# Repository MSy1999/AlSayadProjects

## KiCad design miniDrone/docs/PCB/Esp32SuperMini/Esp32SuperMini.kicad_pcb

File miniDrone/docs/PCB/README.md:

# MiniDrone PCB schematic

Open `Esp32SuperMini/Esp32SuperMini.kicad_pro` in KiCad 10, then open its
schematic. If the schematic is already open, close and reopen it so KiCad
loads the updated file. The original empty schematic is saved in
`Esp32SuperMini/references/original-empty.kicad_sch`.

This is a carrier for the existing ESP32-C3 Super Mini and GY-521/MPU6050 boards,
using four BC337 low-side motor switches and your 1S 3.7 V, 400 mAh battery.
The schematic and routed PCB are prototypes for review; module fit and motor
current ratings still require validation before manufacture.

Revision D uses a 70 x 70 mm board with extra space for hand soldering and
through-hole carrier components: ordinary 1/4 W axial resistors,
leaded capacitors and diodes, BC337s, and solderable header/socket holes for both
modules. No SMD assembly is required on the carrier. See
[hand assembly and part sizes](HAND_ASSEMBLY.md). The previous SMD revision is
archived under `Esp32SuperMini/references/revision-B-SMD/`.

The schematic uses one A2 sheet with continuous visible wires between the battery,
power components, controller, IMU and all four motor stages. Labels name the
wires; no connection relies on matching labels. A dot marks a joined branch;
crossing wires without a dot remain separate. The controller symbol now groups
its pins by function to simplify wiring, while preserving the physical header
pad numbers listed below.

## Files

- `Esp32SuperMini.kicad_sch`: editable schematic with all four motor stages.
- `MiniDrone.kicad_sym`: project-local Super Mini and GY-521 module symbols.
- `MiniDrone.pretty/ESP32_C3_SuperMini_THT.kicad_mod`: provisional carrier footprint.
- `sym-lib-table` and `fp-lib-table`: relative library paths; no global installation needed.
- `preview/Esp32SuperMini.svg` and `.png`: rendered schematic previews.
- `BOM.csv`: components, assigned footprints and unresolved design notes.
- `MiniDrone.net.xml`: exported electrical connectivity.
- `erc-report.json`: KiCad electrical rules report.

Paths above are relative to `Esp32SuperMini/`. The project now includes a routed
70 x 70 mm PCB with two copper layers, ground pours, an antenna copper keepout,
four M2 mounting holes and labeled motor connectors at the corners. See
[PCB layout details](PCB_LAYOUT.md) for geometry, previews and validation results.

## If KiCad reports the Super Mini footprint is not found

The project library is `MiniDrone`, with path `${KIPRJMOD}/MiniDrone.pretty`.
If the editors were already open when the library files were created, refresh
the loaded table:

1. Close the **Update PCB from Schematic** dialog.
2. In PCB Editor, open **Preferences > Manage Footprint Libraries** and select
   **Project Specific Libraries**. Confirm that `MiniDrone` is enabled and its
   path is `${KIPRJMOD}/MiniDrone.pretty`.
3. Click **OK** to reload the footprint libraries, then press **F8** again.

This refresh was verified in the running KiCad session: U1 was found and the
update preview reported zero warnings and zero errors. Keep the `.pretty`
directory and `fp-lib-table` alongside the project when copying it elsewhere.

## The Super Mini symbol

The Super Mini is a development board, not the ESP32-C3 IC and not an
ESP32-C3-MINI-1 RF module. Those components have different pinouts and footprints.
Use `MiniDrone:ESP32_C3_SUPER_MINI` in this project. It represents the headers;
the regulator, USB connector, crystal, reset, boot button and antenna remain on
the existing plug-in board.

Looking from the top with the USB connector at the top:

| Left pad, top to bottom | Signal | Right pad, top to bottom | Signal |
| --- | --- | --- | --- |
| 1 | GPIO5 / IMU SCL | 16 | 5V |
| 2 | GPIO6 / M1 front left | 15 | GND |
| 3 | GPIO7 / M2 front right | 14 | 3V3 |
| 4 | GPIO8 / unused | 13 | GPIO4 / IMU SDA |
| 5 | GPIO9 / unused | 12 | GPIO3 / unused |
| 6 | GPIO10 / M3 rear right | 11 | GPIO2 / unused |
| 7 | GPIO20 / M4 rear left | 10 | GPIO1 / unused |
| 8 | GPIO21 / unused | 9 | GPIO0 / battery ADC |

These are carrier pad numbers, not chip pin numbers. They match the project
pinout image and firmware. Before making a board, measure the physical Super
Mini: this draft assumes 2.54 mm header pitch, 15.24 mm row spacing and an
18 x 22.5 mm board outline. Clone dimensions can differ. Check the USB overhang
and socket height. The antenna area is marked on `Dwgs.User`; create an actual
all-layer copper/track/via keepout during layout and verify its extent against
the physical antenna. The library drawing alone is not an enforced keepout;
the routed PCB includes a separate all-copper-layer rule area at the antenna.

U2 uses the assumed GY-521 header order VCC, GND, SCL, SDA, XDA, XCL, AD0, INT.
Verify this order on your board. Its footprint describes the 8-pin header only;
the module outline and mounting holes have not been measured.

## Power circuit

Battery positive -> J1 pin 1 -> external main switch SW1 -> `VBAT_SW`.
The four motor positive terminals connect to `VBAT_SW`; motor negative terminals
connect to their BC337 collectors. All emitters and logic grounds share GND.

J2 is a **wired interface to an external regulated 5 V boost module**, not the
footprint of a particular regulator. Pin 1 = battery input positive, 2 = input
ground, 3 = regulated 5 V output, 4 = output ground. Choose a module verified to
deliver at least 0.5 A at 5 V across the usable 1S battery range. Confirm its pin
order and connect with wires as needed. Its internal circuit is not implemented
on this carrier.

JP1 connects the boost output to the Super Mini's 5V input; its existing onboard
regulator supplies 3V3 to the controller and sensor. This deliberately uses the
development board's 5V input rather than assuming its regulator tolerates power
injected into 3V3. It differs from the earlier generic buck-boost proposal in
`../WIRING.md`.

- Battery operation: USB unplugged, JP1 removable shunt installed.
- USB programming: battery switch OFF, JP1 shunt REMOVED, then connect USB.
- JP1 is a manual isolation link, not automatic USB/battery power OR-ing.

The battery must have appropriate protection and discharge capability. Capacity
alone does not specify discharge current. No charger, automatic low-voltage
cutoff or reverse-polarity protection is included. The current sensor-monitor
firmware does not sample the battery divider or implement battery protection.

## BC337 motor drivers: values to verify

Each channel has a 330 ohm series base resistor (provisional), 10 kohm
base-emitter pulldown, leaded 1N5819 Schottky flyback diode (provisional), and 100 nF
ceramic suppression capacitor. The diode cathode/striped end goes to battery
positive and its anode goes to the collector/motor negative. Place the 100 nF
at the physical motor terminals; a distant PCB capacitor is not equivalent.

The selected BC337 footprint assumes onsemi's pin numbering: 1 collector,
2 base, 3 emitter. Verify the datasheet for your actual supplier. Do not reuse
a MOSFET pin assignment for a BC337.

At 3.3 V, 330 ohm gives roughly 6-8 mA of base drive depending on the base
voltage. This does not guarantee saturation at the unknown motor startup or
stall current. The onsemi BC337 datasheet specifies its saturation test at
500 mA collector current with 50 mA base current; the 800 mA absolute maximum
collector rating is not a practical design target. Do not reduce the resistor
to demand that base current directly from an ESP32 pin. Measure startup/stall
current, transistor voltage drop and temperature; use a suitable 3.3 V
logic-level MOSFET or proper driver if the BC337 stage is insufficient.

The 1N5819 selection, main switch, battery/motor connectors, copper widths and
battery discharge rating must also be checked against measured current. The
2.54 mm header footprints are placeholders for prototype wiring; they are not
verified high-current connector selections. C1's 470 uF value is a starting
point for measuring motor-induced supply transients, not a validated result.

R9/R10 are marked DNP in KiCad. Populate the optional 4.7 kohm I2C pull-ups only
if the GY-521 does not already supply suitable pull-ups to 3.3 V.

## Validation and regeneration

Validated with KiCad CLI 10.0.7: schematic loaded, SVG exported, and ERC produced
zero errors and zero warnings. `validate_schematic.py` checks the exported nets
against `main/board.h`, all four driver topologies, diode polarity, controller
power, sensor connections and battery divider. It also checks that every
assigned footprint exists. These checks do not validate thermal ratings or fit.
Revision B also compares every exported net's component/pin membership against
revision A and checks that there are no repeated or off-sheet labels, so the
connections are preserved using the visible wires.

`generate_schematic.py` regenerates the schematic, custom library, footprint
and BOM. **It overwrites the generated schematic**, so save manual edits
elsewhere before running it. `inspect_symbols.py` supplies its library reader.
`wired_layout.py` defines the fully connected page arrangement. The generator
uses KiCad's standard symbol libraries at the installed Windows
KiCad 10 path; edit `BASE` if using another installation.

```powershell
python docs/PCB/generate_schematic.py
& 'C:\Program Files\KiCad\10.0\bin\kicad-cli.exe' sch erc --format json --output docs/PCB/Esp32SuperMini/erc-report.json docs/PCB/Esp32SuperMini/Esp32SuperMini.kicad_sch
& 'C:\Program Files\KiCad\10.0\bin\kicad-cli.exe' sch export netlist --format kicadxml --output docs/PCB/Esp32SuperMini/MiniDrone.net.xml docs/PCB/Esp32SuperMini/Esp32SuperMini.kicad_sch
& 'C:\Program Files\KiCad\10.0\bin\kicad-cli.exe' sch export svg --output docs/PCB/Esp32SuperMini/preview docs/PCB/Esp32SuperMini/Esp32SuperMini.kicad_sch
python docs/PCB/validate_schematic.py
python docs/PCB/render_preview.py
```

The optional PNG renderer needs `resvg-py`; the editable schematic and SVG do
not depend on it. The generator makes no firmware changes.

## Circuit references

- [Super Mini pinout and board notes in Apache NuttX](https://nuttx.incubator.apache.org/docs/latest/platforms/risc-v/esp32c3/boards/esp32c3-supermini/index.html).
- [Supplier-hosted Super Mini pinout/schematic PDF](https://dl.artronshop.co.th/ESP32-C3%20SuperMini%20datasheet.pdf): a reference link for comparing your board variant; the remote PDF download timed out in this session, so it was not used to verify internal circuitry.
- [ded811's editable KiCad Super Mini circuit](https://github.com/ded811/ESP32-C3-Super-Mini-Kicad): a third-party redesign with antenna changes, not guaranteed identical to the purchased board.
- [Espressif ESP32-C3 hardware design checklist](https://docs.espressif.com/projects/esp-hardware-design-guidelines/en/latest/esp32c3/schematic-checklist.html): supply and GPIO guidance.
- [onsemi BC337 datasheet](https://www.onsemi.com/pdf/datasheet/bc337-fsc-d.pdf): assumed transistor pinout and saturation conditions.
- [Vishay 1N5819 datasheet](https://www.vishay.com/docs/88525/1n5817.pdf): leaded DO-41 Schottky package and cathode stripe.

Local module symbols and the carrier footprint were created for this project.
Cached standard component symbols originate from the installed KiCad standard
libraries; their library license/exception applies.

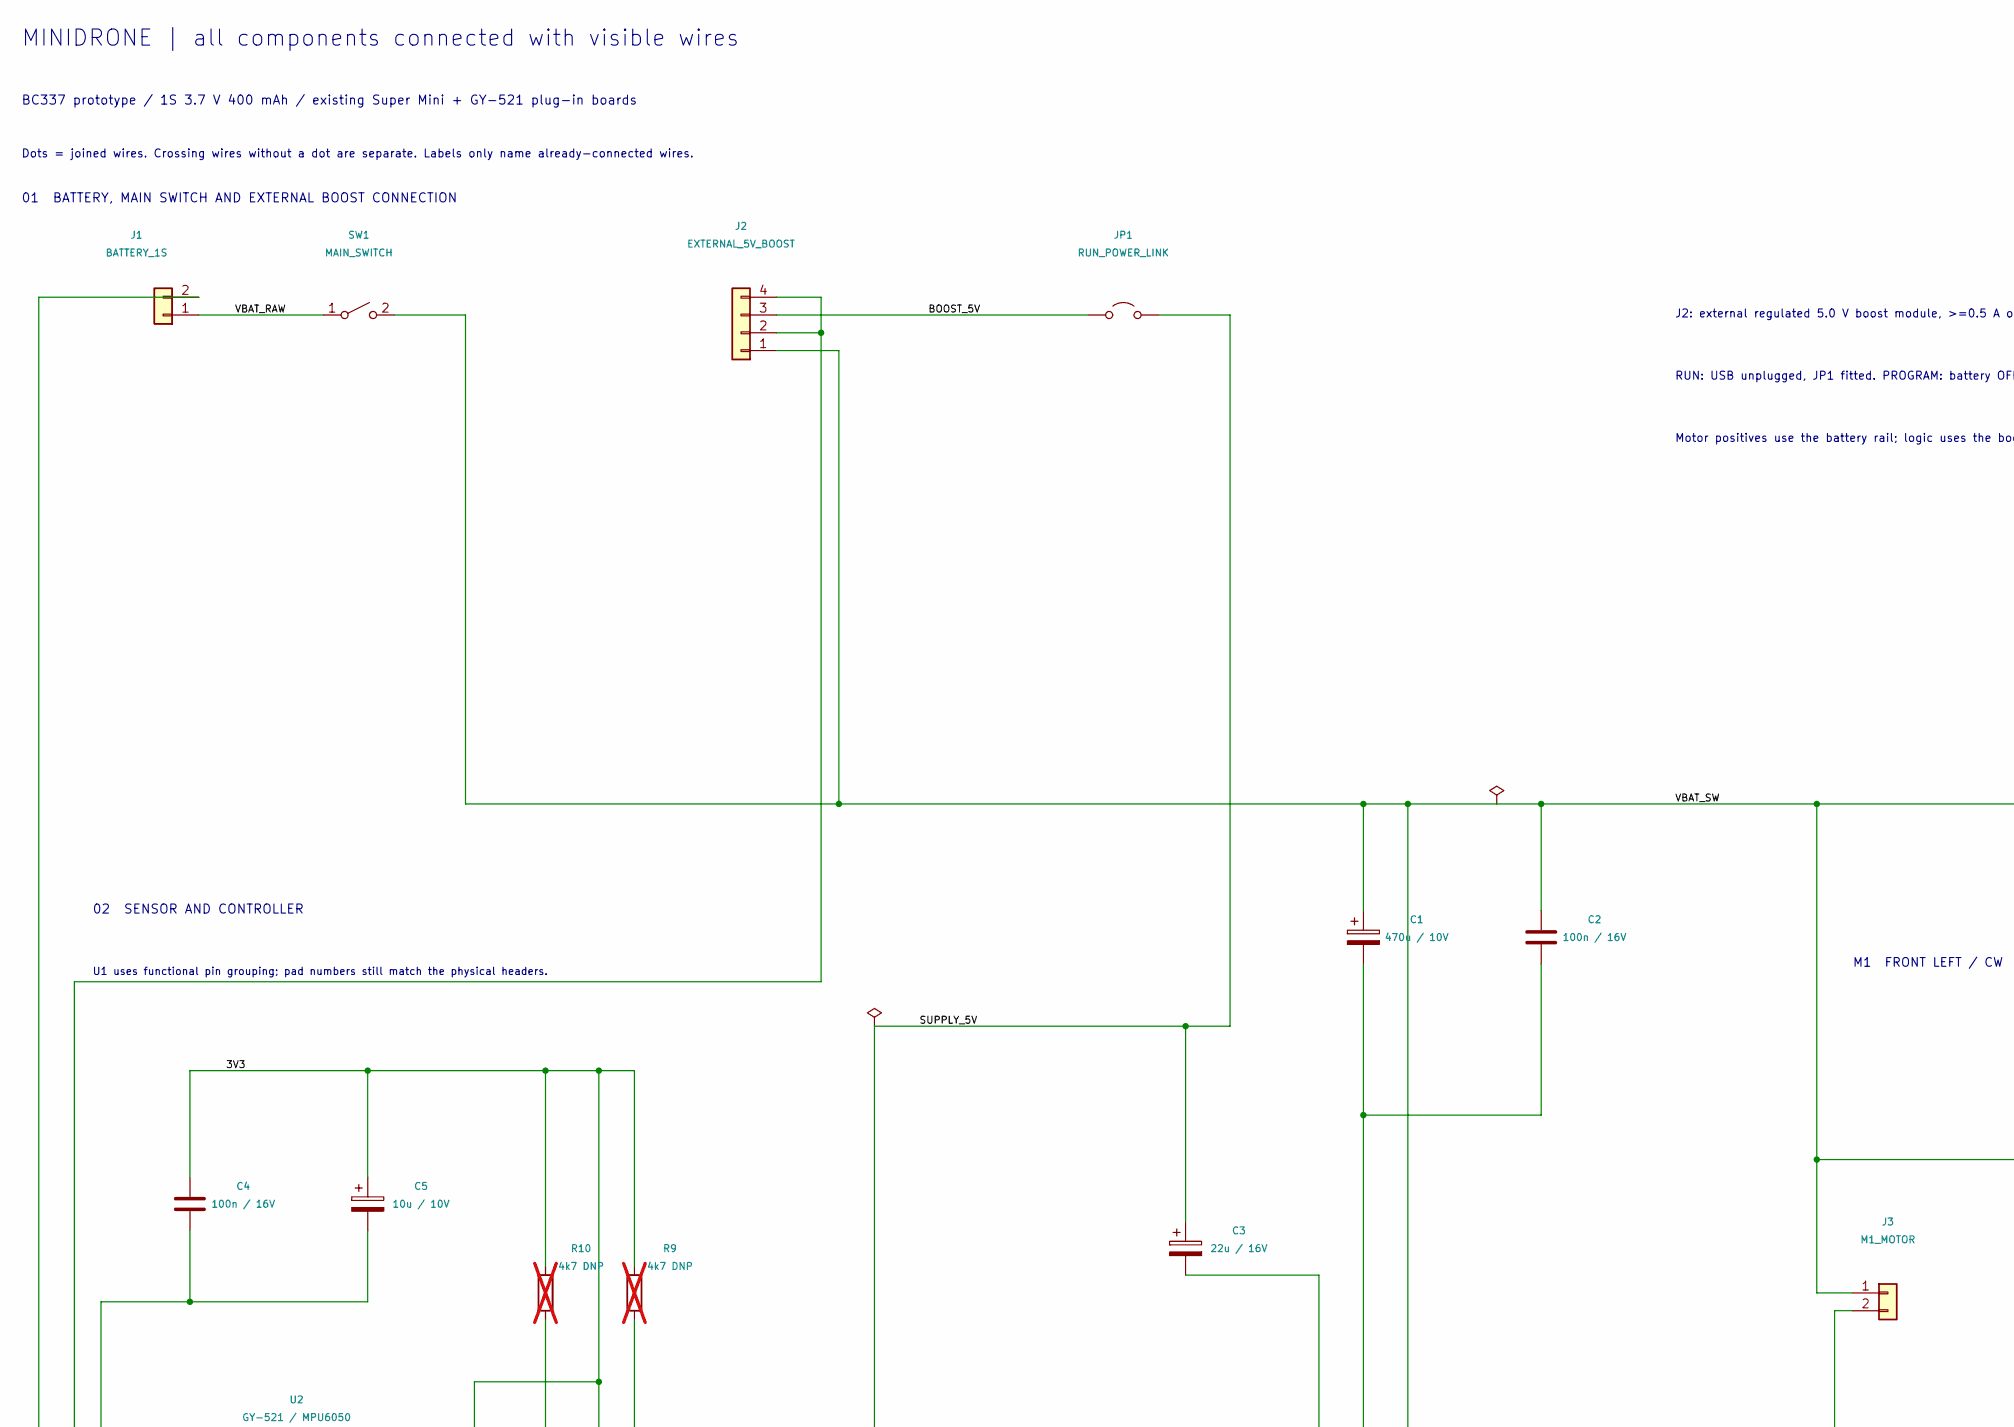
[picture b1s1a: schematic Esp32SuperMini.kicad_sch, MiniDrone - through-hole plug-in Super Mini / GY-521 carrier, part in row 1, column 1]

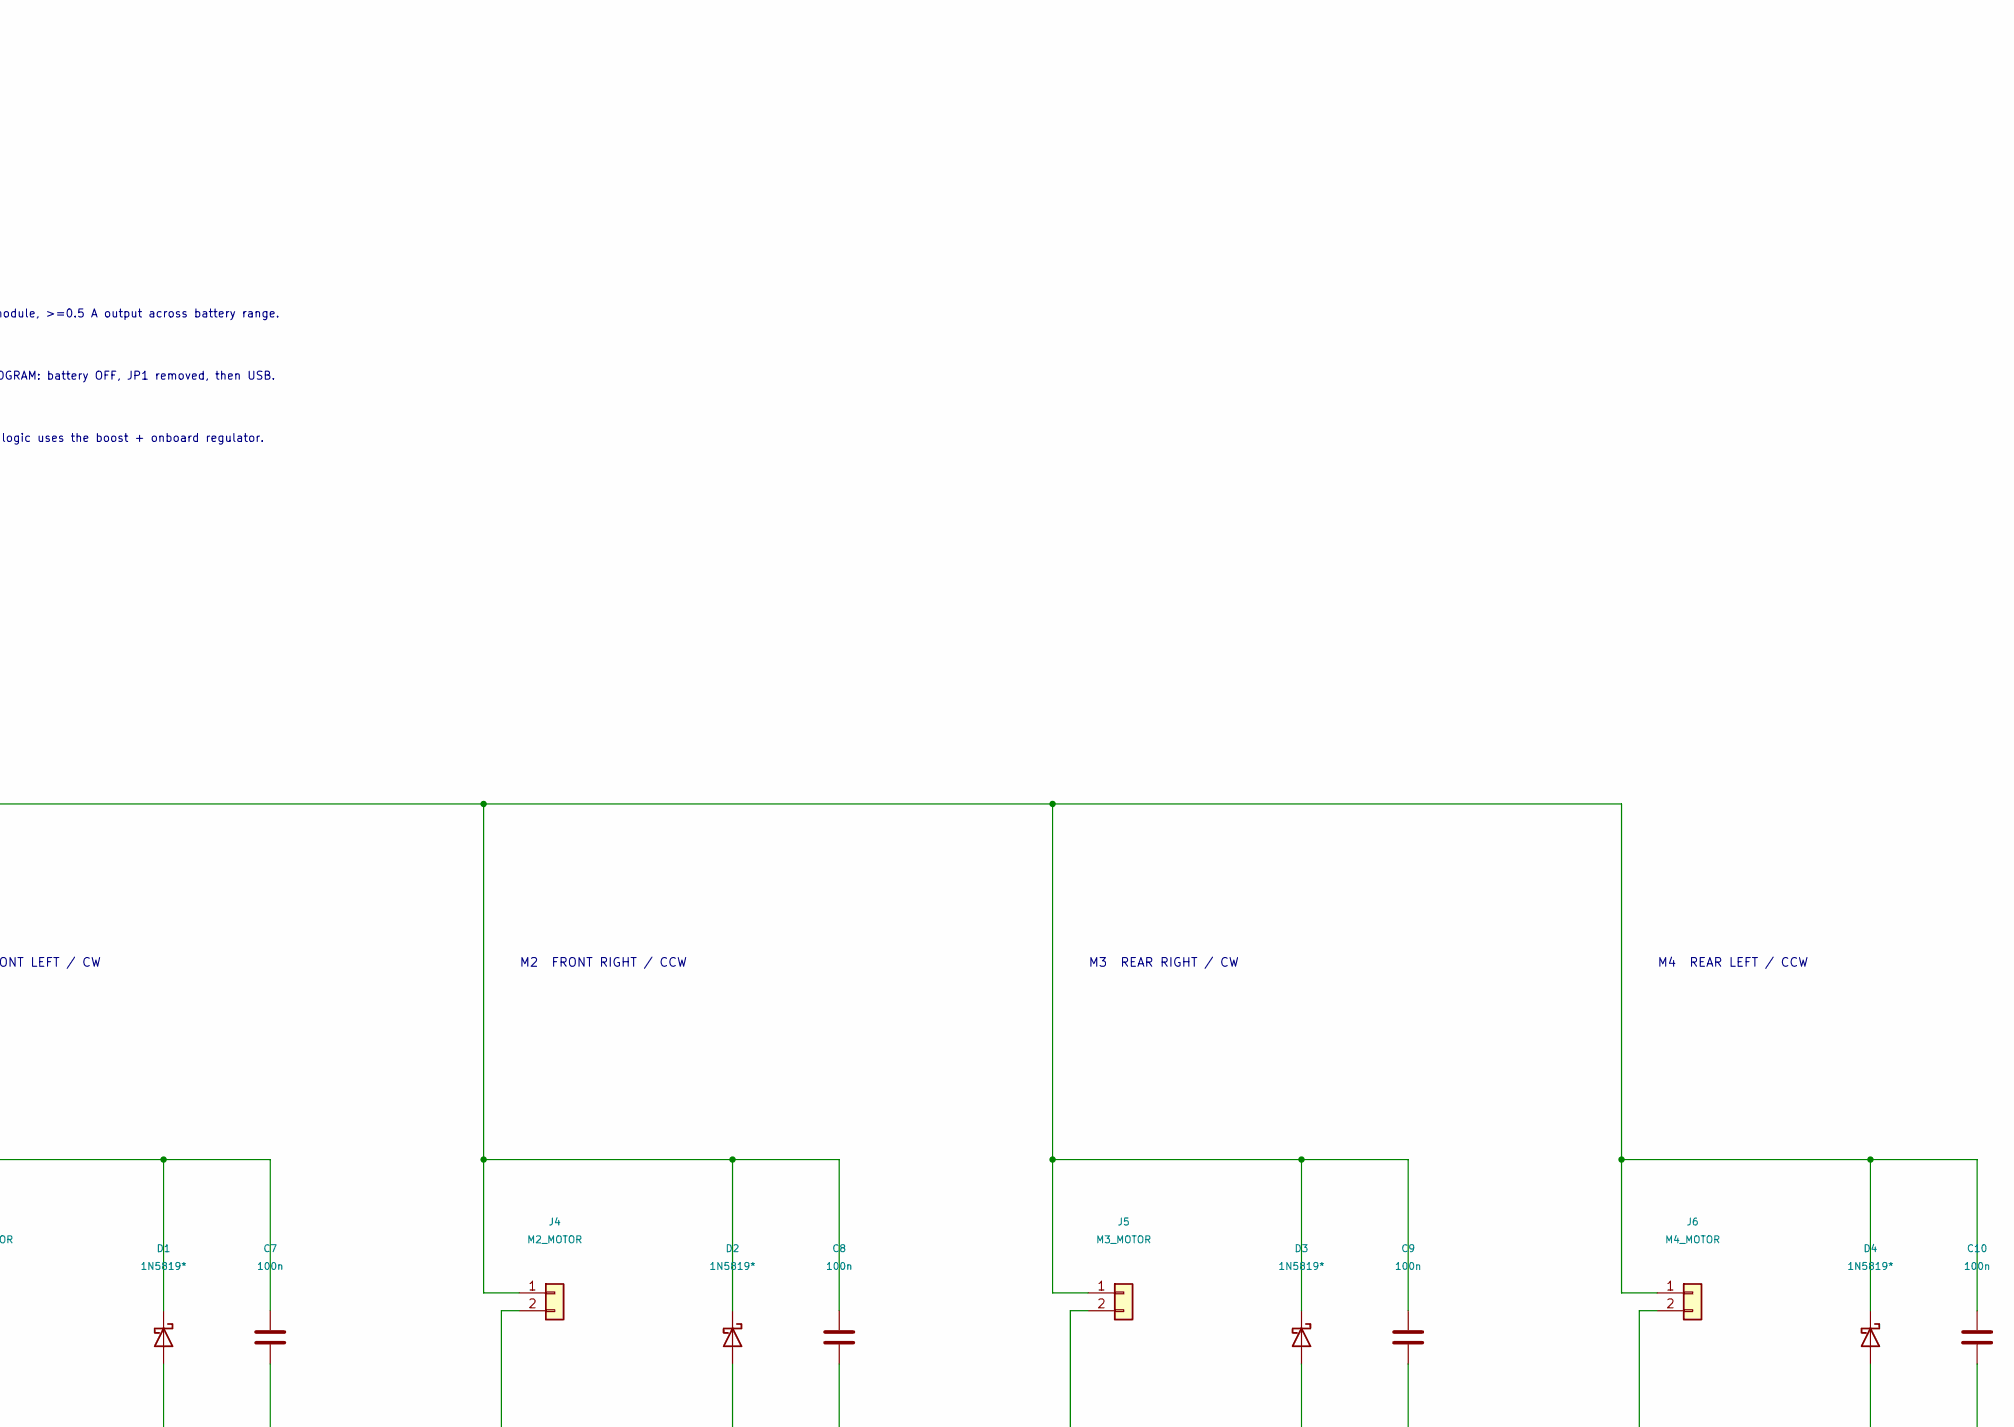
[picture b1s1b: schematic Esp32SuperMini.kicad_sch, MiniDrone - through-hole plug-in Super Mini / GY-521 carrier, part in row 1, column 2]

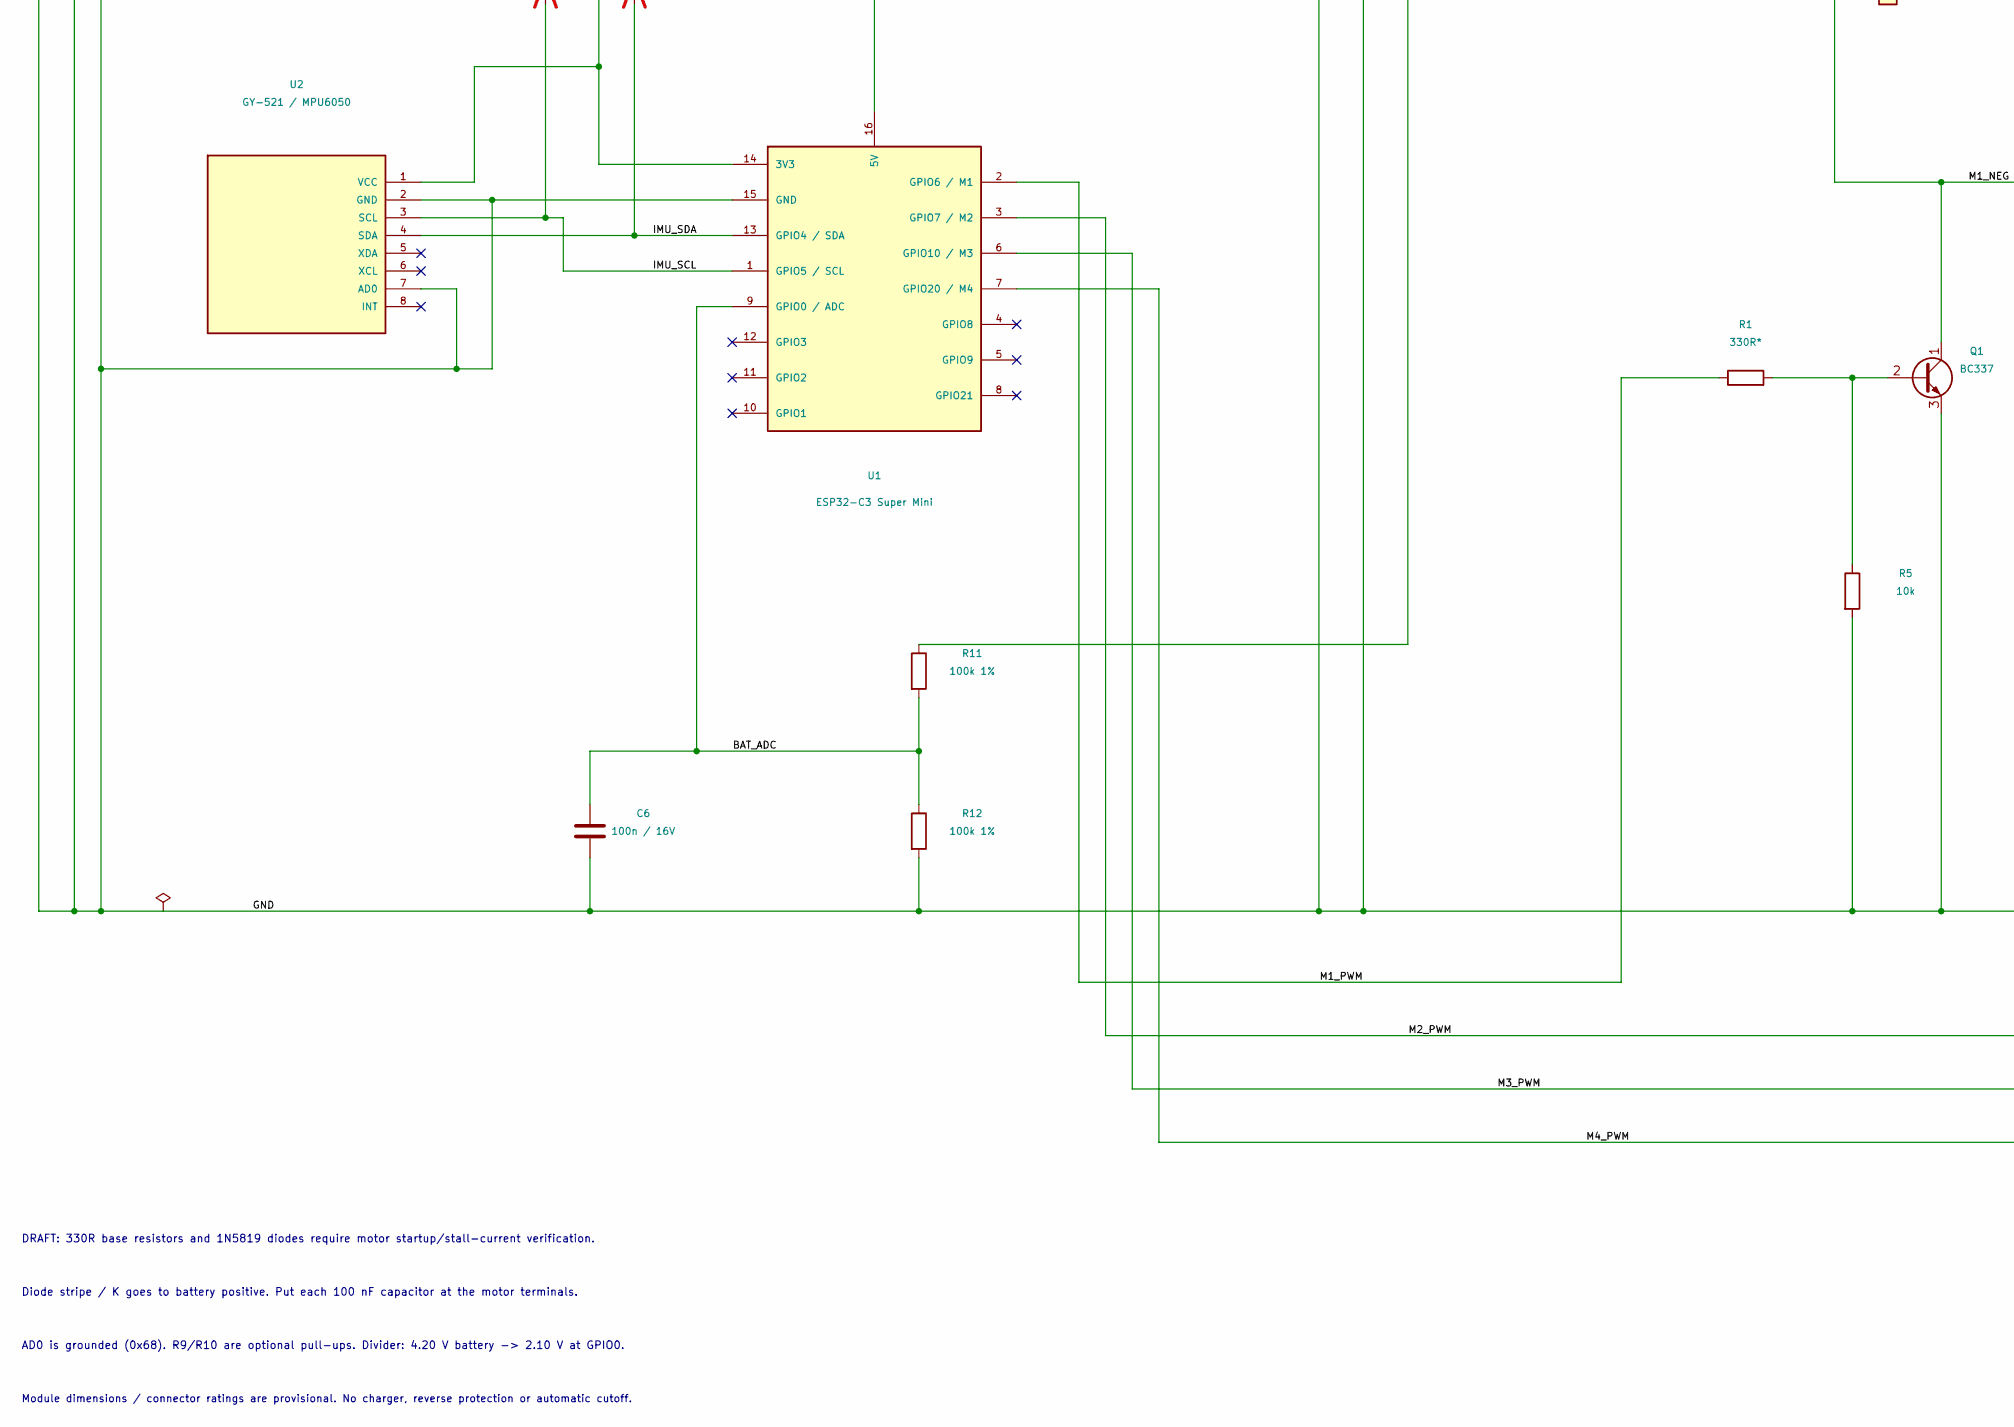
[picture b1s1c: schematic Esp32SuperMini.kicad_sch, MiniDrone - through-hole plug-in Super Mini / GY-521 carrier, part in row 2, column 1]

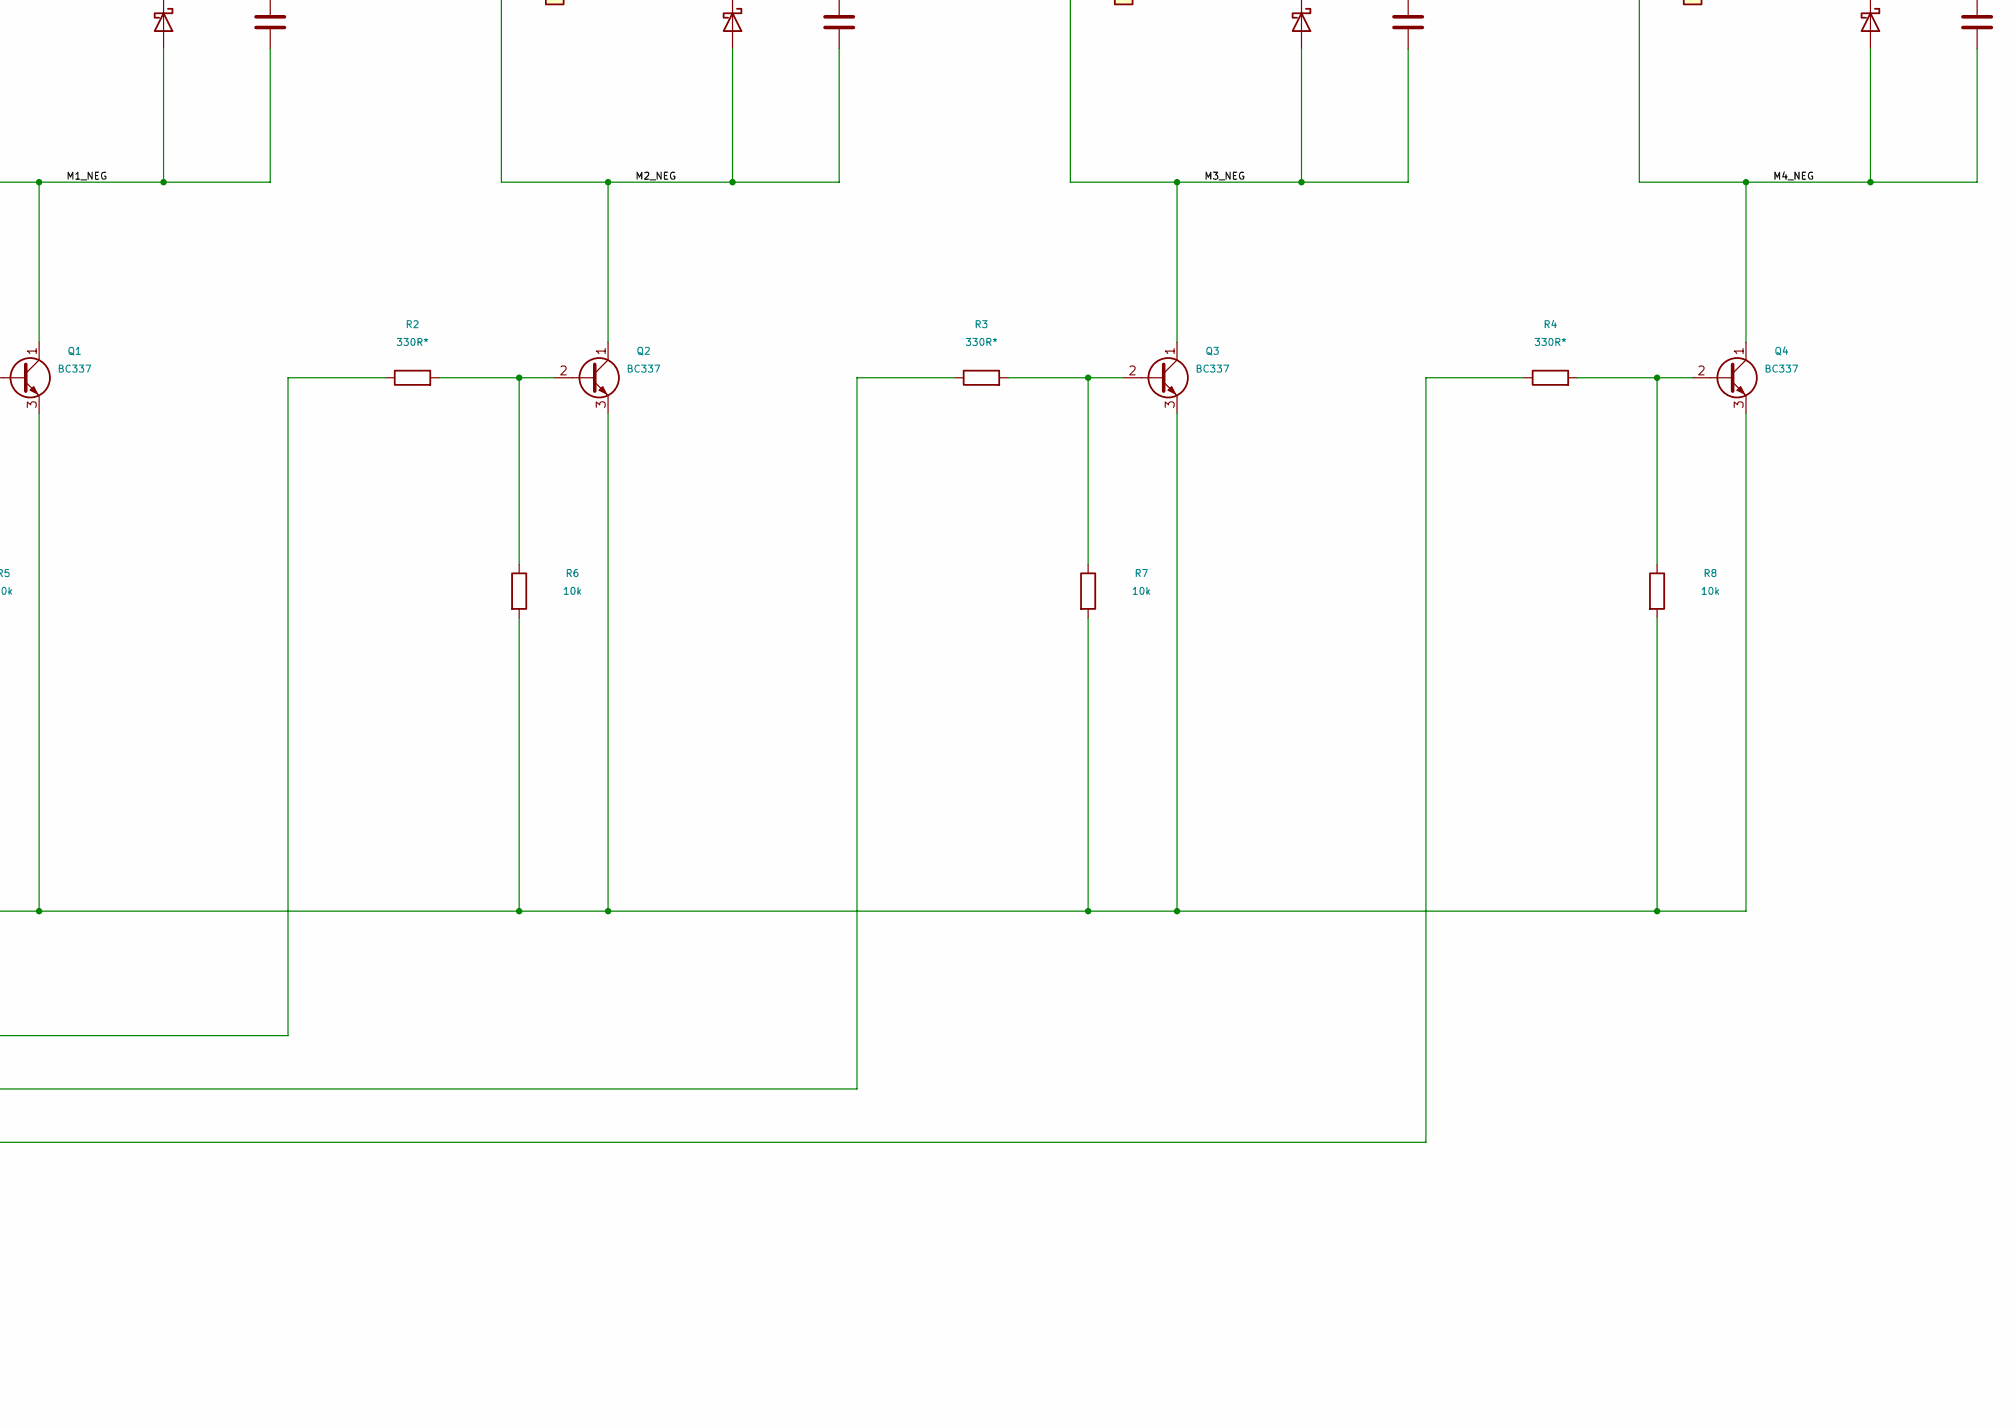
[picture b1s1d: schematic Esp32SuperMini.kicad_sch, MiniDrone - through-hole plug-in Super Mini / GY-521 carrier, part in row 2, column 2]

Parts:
C1: 470u / 10V; CP_Radial_D6.3mm_P2.50mm
C2, C4, C6: 100n / 16V; C_Disc_D5.0mm_W2.5mm_P5.00mm
C3: 22u / 16V; CP_Radial_D5.0mm_P2.00mm
C5: 10u / 10V; CP_Radial_D5.0mm_P2.00mm
C7, C8, C9, C10: 100n; C_Disc_D5.0mm_W2.5mm_P5.00mm
D1, D2, D3, D4: 1N5819*; D_DO-41_SOD81_P10.16mm_Horizontal
J1: BATTERY_1S; PinHeader_1x02_P2.54mm_Vertical
J2: EXTERNAL_5V_BOOST; PinHeader_1x04_P2.54mm_Vertical
J3: M1_MOTOR; PinHeader_1x02_P2.54mm_Vertical
J4: M2_MOTOR; PinHeader_1x02_P2.54mm_Vertical
J5: M3_MOTOR; PinHeader_1x02_P2.54mm_Vertical
J6: M4_MOTOR; PinHeader_1x02_P2.54mm_Vertical
JP1: RUN_POWER_LINK; PinHeader_1x02_P2.54mm_Vertical
Q1, Q2, Q3, Q4: BC337; TO-92_Inline_Wide
R1, R2, R3, R4: 330R*; R_Axial_DIN0207_L6.3mm_D2.5mm_P7.62mm_Horizontal
R5, R6, R7, R8: 10k; R_Axial_DIN0207_L6.3mm_D2.5mm_P7.62mm_Horizontal
R9, R10: 4k7 DNP; R_Axial_DIN0207_L6.3mm_D2.5mm_P7.62mm_Horizontal; not fitted
R11, R12: 100k 1%; R_Axial_DIN0207_L6.3mm_D2.5mm_P7.62mm_Horizontal
SW1: MAIN_SWITCH; PinHeader_1x02_P2.54mm_Vertical
U1: ESP32-C3 Super Mini; ESP32_C3_SuperMini_THT
U2: GY-521 / MPU6050; PinSocket_1x08_P2.54mm_Vertical

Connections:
/3V3: C4.1, C5.1, R9.1, R10.1, U1.14 (3V3), U2.1 (VCC)
/BAT_ADC: C6.1, R11.2, R12.1, U1.9 (GPIO0 / ADC)
/BOOST_5V: J2.3, JP1.1 (A)
/GND: C1.2, C2.2, C3.2, C4.2, C5.2, C6.2, J1.2, J2.2, J2.4, Q1.3 (E), Q2.3 (E), Q3.3 (E), Q4.3 (E), R5.2, R6.2, R7.2, R8.2, R12.2, U1.15 (GND), U2.2 (GND), U2.7 (AD0)
/IMU_SCL: R10.2, U1.1 (GPIO5 / SCL), U2.3 (SCL)
/IMU_SDA: R9.2, U1.13 (GPIO4 / SDA), U2.4 (SDA)
/M1_NEG: C7.2, D1.2 (A), J3.2, Q1.1 (C)
/M1_PWM: R1.1, U1.2 (GPIO6 / M1)
/M2_NEG: C8.2, D2.2 (A), J4.2, Q2.1 (C)
/M2_PWM: R2.1, U1.3 (GPIO7 / M2)
/M3_NEG: C9.2, D3.2 (A), J5.2, Q3.1 (C)
/M3_PWM: R3.1, U1.6 (GPIO10 / M3)
/M4_NEG: C10.2, D4.2 (A), J6.2, Q4.1 (C)
/M4_PWM: R4.1, U1.7 (GPIO20 / M4)
/SUPPLY_5V: C3.1, JP1.2 (B), U1.16 (5V)
/VBAT_RAW: J1.1, SW1.1 (A)
/VBAT_SW: C1.1, C2.1, C7.1, C8.1, C9.1, C10.1, D1.1 (K), D2.1 (K), D3.1 (K), D4.1 (K), J2.1, J3.1, J4.1, J5.1, J6.1, R11.1, SW1.2 (B)
unnamed: Q1.2 (B), R1.2, R5.1
unnamed: Q2.2 (B), R2.2, R6.1
unnamed: Q3.2 (B), R3.2, R7.1
unnamed: Q4.2 (B), R4.2, R8.1

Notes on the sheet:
MINIDRONE | all components connected with visible wires
BC337 prototype / 1S 3.7 V 400 mAh / existing Super Mini + GY-521 plug-in boards
Dots = joined wires. Crossing wires without a dot are separate. Labels only name already-connected wires.
01 BATTERY, MAIN SWITCH AND EXTERNAL BOOST CONNECTION
J2: external regulated 5.0 V boost module, >=0.5 A output across battery range.
RUN: USB unplugged, JP1 fitted. PROGRAM: battery OFF, JP1 removed, then USB.
Motor positives use the battery rail; logic uses the boost + onboard regulator.
02 SENSOR AND CONTROLLER
U1 uses functional pin grouping; pad numbers still match the physical headers.
M1 FRONT LEFT / CW
M2 FRONT RIGHT / CCW
M3 REAR RIGHT / CW
M4 REAR LEFT / CCW
DRAFT: 330R base resistors and 1N5819 diodes require motor startup/stall-current verification.
Diode stripe / K goes to battery positive. Put each 100 nF capacitor at the motor terminals.
AD0 is grounded (0x68). R9/R10 are optional pull-ups. Divider: 4.20 V battery -> 2.10 V at GPIO0.
Module dimensions / connector ratings are provisional. No charger, reverse protection or automatic cutoff.

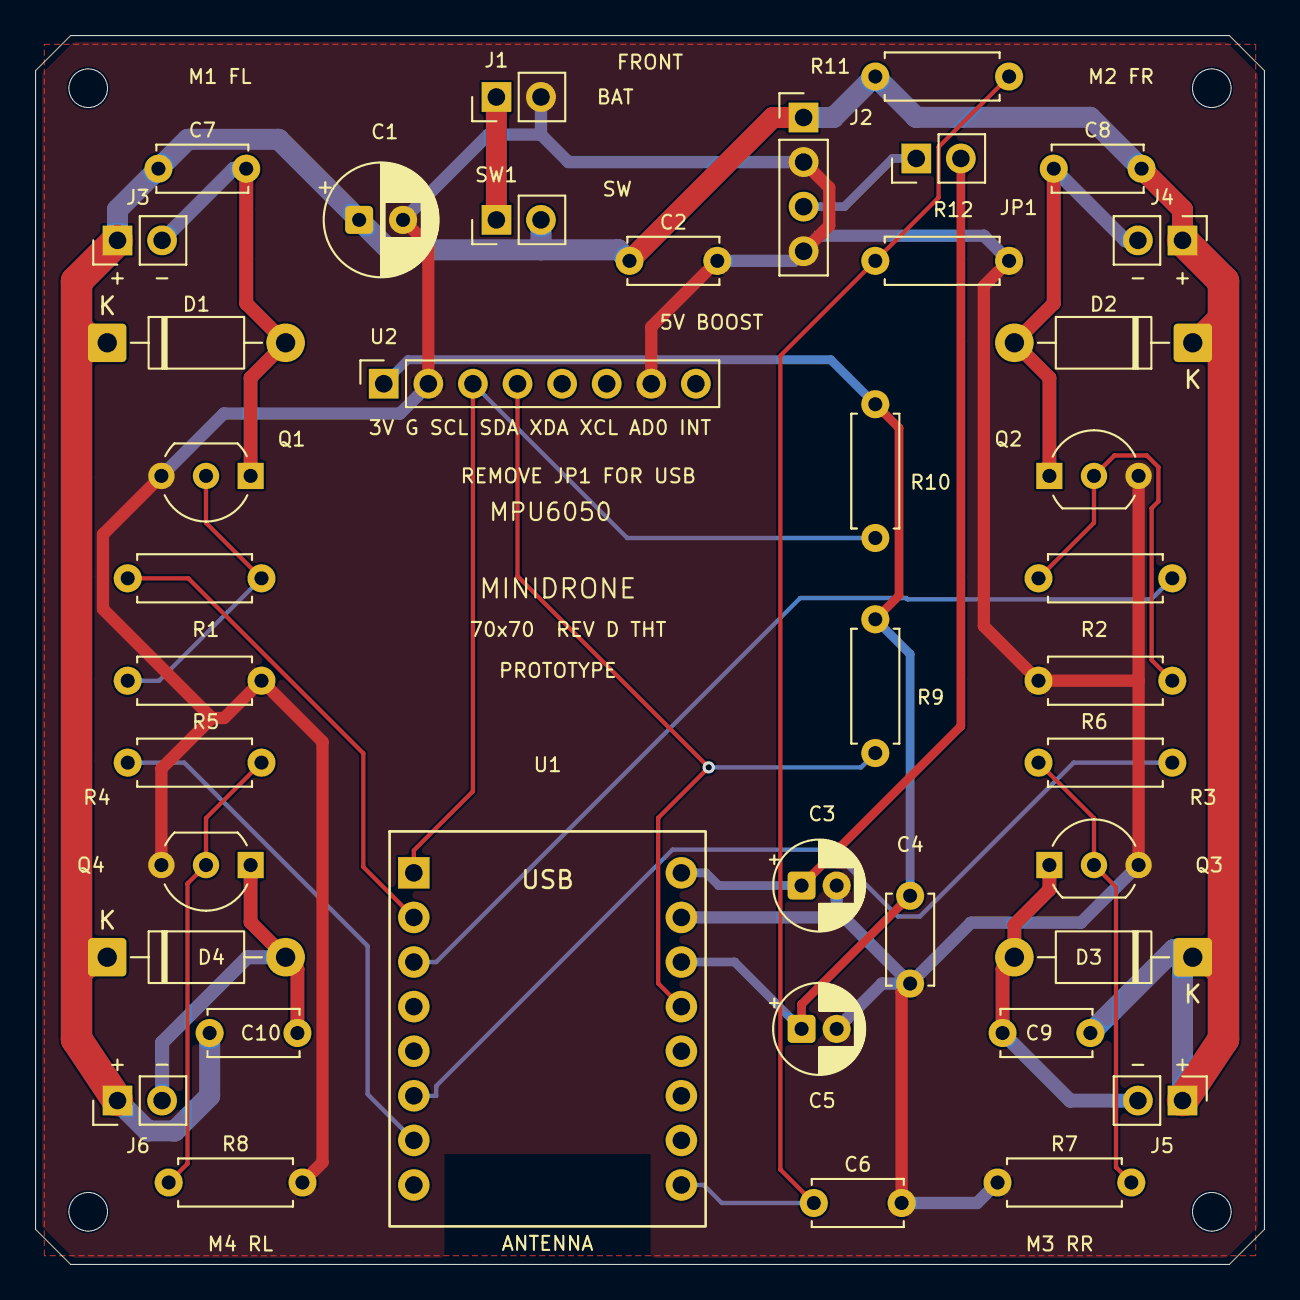
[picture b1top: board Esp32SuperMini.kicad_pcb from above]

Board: 2 copper layers, 70.0 x 70.0 mm, 44 parts (0 on the bottom side), 21 nets.

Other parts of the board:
H1, H2, H3, H4: MountingHole_2.2mm_M2

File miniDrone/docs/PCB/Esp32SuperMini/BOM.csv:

Reference,Value,Footprint,Design note
J1,BATTERY_1S,Connector_PinHeader_2.54mm:PinHeader_1x02_P2.54mm_Vertical,"3.7 V nominal, 4.2 V full; 400 mAh. Connector/discharge rating TBD."
SW1,MAIN_SWITCH,Connector_PinHeader_2.54mm:PinHeader_1x02_P2.54mm_Vertical,External switch via header; total motor stall current + logic input current.
J2,EXTERNAL_5V_BOOST,Connector_PinHeader_2.54mm:PinHeader_1x04_P2.54mm_Vertical,"Wired module interface: 1 IN+, 2 IN-/GND, 3 OUT+ 5V, 4 OUT-/GND."
JP1,RUN_POWER_LINK,Connector_PinHeader_2.54mm:PinHeader_1x02_P2.54mm_Vertical,REMOVABLE shunt. REMOVE and switch battery OFF before USB.
C1,470u / 10V,Capacitor_THT:CP_Radial_D6.3mm_P2.50mm,
C2,100n / 16V,Capacitor_THT:C_Disc_D5.0mm_W2.5mm_P5.00mm,
C3,22u / 16V,Capacitor_THT:CP_Radial_D5.0mm_P2.00mm,
C4,100n / 16V,Capacitor_THT:C_Disc_D5.0mm_W2.5mm_P5.00mm,
C5,10u / 10V,Capacitor_THT:CP_Radial_D5.0mm_P2.00mm,
U1,ESP32-C3 Super Mini,MiniDrone:ESP32_C3_SuperMini_THT,Plug-in board; verify physical dimensions before layout.
U2,GY-521 / MPU6050,Connector_PinSocket_2.54mm:PinSocket_1x08_P2.54mm_Vertical,"Verify actual header order VCC,GND,SCL,SDA,XDA,XCL,AD0,INT."
R9,4k7 DNP,Resistor_THT:R_Axial_DIN0207_L6.3mm_D2.5mm_P7.62mm_Horizontal,Optional: do not populate if suitable 3V3 pull-ups are already on GY-521.
R10,4k7 DNP,Resistor_THT:R_Axial_DIN0207_L6.3mm_D2.5mm_P7.62mm_Horizontal,Optional: do not populate if suitable 3V3 pull-ups are already on GY-521.
R11,100k 1%,Resistor_THT:R_Axial_DIN0207_L6.3mm_D2.5mm_P7.62mm_Horizontal,
R12,100k 1%,Resistor_THT:R_Axial_DIN0207_L6.3mm_D2.5mm_P7.62mm_Horizontal,
C6,100n / 16V,Capacitor_THT:C_Disc_D5.0mm_W2.5mm_P5.00mm,
Q1,BC337,Package_TO_SOT_THT:TO-92_Inline_Wide,"Assumed onsemi pinout 1 C, 2 B, 3 E. Verify your transistor supplier."
R1,330R*,Resistor_THT:R_Axial_DIN0207_L6.3mm_D2.5mm_P7.62mm_Horizontal,PROVISIONAL base resistor; verify motor startup current and transistor saturation.
R5,10k,Resistor_THT:R_Axial_DIN0207_L6.3mm_D2.5mm_P7.62mm_Horizontal,
J3,M1_MOTOR,Connector_PinHeader_2.54mm:PinHeader_1x02_P2.54mm_Vertical,"Motor + pin1, motor - pin2. Connector current rating TBD."
D1,1N5819*,Diode_THT:D_DO-41_SOD81_P10.16mm_Horizontal,Leaded DO-41 Schottky; verify motor current/thermal ratings. Stripe to VBAT_SW.
C7,100n,Capacitor_THT:C_Disc_D5.0mm_W2.5mm_P5.00mm,"16V ceramic, fit directly at motor terminals."
Q2,BC337,Package_TO_SOT_THT:TO-92_Inline_Wide,"Assumed onsemi pinout 1 C, 2 B, 3 E. Verify your transistor supplier."
R2,330R*,Resistor_THT:R_Axial_DIN0207_L6.3mm_D2.5mm_P7.62mm_Horizontal,PROVISIONAL base resistor; verify motor startup current and transistor saturation.
R6,10k,Resistor_THT:R_Axial_DIN0207_L6.3mm_D2.5mm_P7.62mm_Horizontal,
J4,M2_MOTOR,Connector_PinHeader_2.54mm:PinHeader_1x02_P2.54mm_Vertical,"Motor + pin1, motor - pin2. Connector current rating TBD."
D2,1N5819*,Diode_THT:D_DO-41_SOD81_P10.16mm_Horizontal,Leaded DO-41 Schottky; verify motor current/thermal ratings. Stripe to VBAT_SW.
C8,100n,Capacitor_THT:C_Disc_D5.0mm_W2.5mm_P5.00mm,"16V ceramic, fit directly at motor terminals."
Q3,BC337,Package_TO_SOT_THT:TO-92_Inline_Wide,"Assumed onsemi pinout 1 C, 2 B, 3 E. Verify your transistor supplier."
R3,330R*,Resistor_THT:R_Axial_DIN0207_L6.3mm_D2.5mm_P7.62mm_Horizontal,PROVISIONAL base resistor; verify motor startup current and transistor saturation.
R7,10k,Resistor_THT:R_Axial_DIN0207_L6.3mm_D2.5mm_P7.62mm_Horizontal,
J5,M3_MOTOR,Connector_PinHeader_2.54mm:PinHeader_1x02_P2.54mm_Vertical,"Motor + pin1, motor - pin2. Connector current rating TBD."
D3,1N5819*,Diode_THT:D_DO-41_SOD81_P10.16mm_Horizontal,Leaded DO-41 Schottky; verify motor current/thermal ratings. Stripe to VBAT_SW.
C9,100n,Capacitor_THT:C_Disc_D5.0mm_W2.5mm_P5.00mm,"16V ceramic, fit directly at motor terminals."
Q4,BC337,Package_TO_SOT_THT:TO-92_Inline_Wide,"Assumed onsemi pinout 1 C, 2 B, 3 E. Verify your transistor supplier."
R4,330R*,Resistor_THT:R_Axial_DIN0207_L6.3mm_D2.5mm_P7.62mm_Horizontal,PROVISIONAL base resistor; verify motor startup current and transistor saturation.
R8,10k,Resistor_THT:R_Axial_DIN0207_L6.3mm_D2.5mm_P7.62mm_Horizontal,
J6,M4_MOTOR,Connector_PinHeader_2.54mm:PinHeader_1x02_P2.54mm_Vertical,"Motor + pin1, motor - pin2. Connector current rating TBD."
D4,1N5819*,Diode_THT:D_DO-41_SOD81_P10.16mm_Horizontal,Leaded DO-41 Schottky; verify motor current/thermal ratings. Stripe to VBAT_SW.
C10,100n,Capacitor_THT:C_Disc_D5.0mm_W2.5mm_P5.00mm,"16V ceramic, fit directly at motor terminals."
